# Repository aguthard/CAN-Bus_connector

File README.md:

# CAN-bridge
CAN-Bus bridge for 3D printer stuff

# Main goal
To provide a simple way to connect two or more CAN-bus motherboards (AFC-light, EBB36, etc.) in 
3D printers and expansion devices such as boxturtle etc.

It's a quick fix, but it works and brings some order to the wiring.

#  BOM

| Quantity | Part |
| ------ | ---- |
| 1 | PCB |
| 1 | Molex Microfit 3.0 vertical receptacle 44769-0401 |
| 2 | Molex Microfit 3.0 right angle thru hole header 43045-0401  |

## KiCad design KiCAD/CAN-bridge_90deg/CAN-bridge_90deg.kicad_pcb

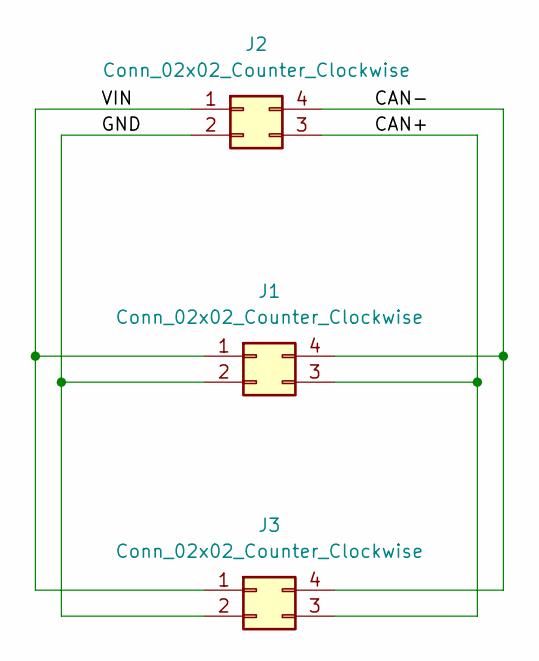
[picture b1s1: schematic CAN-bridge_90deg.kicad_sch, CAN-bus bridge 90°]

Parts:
J1, J3: Conn_02x02_Counter_Clockwise; CONN_SD-43045-001_04_MOL
J2: Conn_02x02_Counter_Clockwise; CONN_SD-44769-001_04_MOL

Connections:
/CAN+: J1.3, J2.3, J3.3
/CAN-: J1.4, J2.4, J3.4
/GND: J1.2, J2.2, J3.2
/VIN: J1.1, J2.1, J3.1

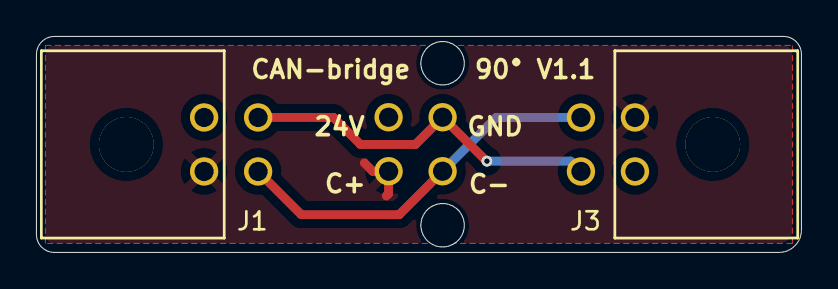
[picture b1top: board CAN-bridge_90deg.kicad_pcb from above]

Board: 2 copper layers, 42.5 x 12.0 mm, 3 parts (1 on the bottom side), 4 nets.

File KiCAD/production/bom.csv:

Designator,Footprint,Quantity,Value,LCSC Part #
"J1, J3",CONN_SD-43045-001_04_MOL,2,Conn_02x02_Counter_Clockwise,
J2,CONN_SD-44769-001_04_MOL,1,Conn_02x02_Counter_Clockwise,

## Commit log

2025-04-11 Test
2025-04-11 Rearanged 3D model step files
2025-04-20 rearranged directories added 90° version
2025-04-20 replaced assembly pdf file
2025-04-20 added can-bridge_90deg.stp

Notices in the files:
KiCAD/CAN-bridge_90deg/CAN-bridge_90deg.kicad_pcb:
(c)2025 GuA
